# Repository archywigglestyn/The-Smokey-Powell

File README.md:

# The-Smokey-Powell
The Particle Photon Wifi Blynk controlled BBQ Smoker controller

This controller reads temperature through a thermistor. Control of your smokers heat is made through a fan or
Solid State relay. It has three extra probe inputs to be used as meat probes.
Wifi is used to connect to the cloud. 

The blynk app is used as the main interface from your phone or mobile device. It is worth noting that all the information runs through the cloud. This means one could be shopping for supplies, while also monitoring ones bbq back at home.

A 4x20 I2c LCD is used as a local display and four buttons as the interface controls.
The local interface is a little clunky. The main interface was intended to be the blynk app.

This controller can use replacement thermistors for Weber iGrill2 grilling thermometer. Or any other thermistor that will work 
with a 10k ohm reference resistor.

For those that use the circuit board I designed. The Outputs are sinking.

Watch The Youtube video for more information.
https://youtu.be/kV1lrQCiiBc

Included are links below or look above in the files.

Version 1.2 Fixes issues with slow internet by using event based communication with blynk compaired to timed.
Also allows smoke percent to be set while in off mode.
Version 1.3, 6-16-19 Renames a variable to an unused name. so that the code will compile.

1.4, 7-4-19 A fellow creator found a variable I forgot to change.
https://go.particle.io/shared_apps/5d1ea377e9731c0017650d83

The Blynk App (Look Above) Download Blynk. In Blynk there is an option take a picture of the QR code.

The circuit board gerber file	(Look Above)  Send this Zip file in to order a board. Board dimensions are 4.75"x2.5"
I may also decide to sell them	 3-29-18 I uploaded V1.1, It has a few minor fixes.

where I have my circuit boards made http://www.pcbunlimited.com/ They are great quality and cheap!
Look for Panel Share. It moves around on the website but it's the cheapest way if you only want one. $19.95 as of 3/15/19

schematic of circuit board	SCH,PDF, and BRD (Look Above)

thingiverse link to make 3d printed cases and DIN mounts https://www.thingiverse.com/thing:3453571

Smokey Powell shopping list:

Bill of Material (Look Above)
digikey (some items are optional) you can use screw terminals or barrel jacks for power, outputs and inputs. Really you can use anything you like that matches the pitch. You could even solder wires directly.
(I have not tested all of the parts on this list yet.)

meat probes, https://www.amazon.com/Weber-iGrill-Pro-Meat-Probe/dp/B01M8LG8U5/ref=sr_1_4?ie=UTF8&qid=1549819424&sr=8-4&keywords=igrill+2+probes

2n2222a or 2n2222 these are cheap and appear to be everywhere except Digikey. Looks like they are becoming obsolete. You will need three of them.	
https://www.amazon.com/2N2222-Plastic-Encapsulate-Power-Transistors-600mA/dp/B06XPWS52G/ref=sr_1_2?ie=UTF8&qid=1530481975&sr=8-2&keywords=2n2222a

This is the particle photon. The brains of the operation.
https://www.amazon.com/Particle-Reprogrammable-Development-Prototyping-Electronics/dp/B016YNU1A0/ref=sr_1_2?ie=UTF8&qid=1550113530&sr=8-2&keywords=photon

Optional items:

5vdc buzzer 12mm use this if you want a microwave like beep for the alarm. Otherwise attach whatever you want to the relay, noise maker, light, spinning flag motor.
	https://www.amazon.com/gp/product/B00B0Q4KKO/ref=oh_aui_detailpage_o02_s00?ie=UTF8&psc=1

SS Relay	these work good if you are going to do some high power electric smoking
	https://www.amazon.com/gp/product/B0087ZTN08/ref=oh_aui_search_detailpage?ie=UTF8&psc=1

Antenna
Add an Antenna for extra range. Be sure to switch the text to external in the program.
	https://www.amazon.com/gp/product/B01GMBUS8O/ref=oh_aui_detailpage_o01_s00?ie=UTF8&psc=1

bbq guru Fan	
If you want to use a fan. This is an option. although it does not like pwm so you need to set the pulse range threshold to 100. Otherwise many 12vdc pc fans work well at about 30%
https://www.bbqguru.com/storenav?CategoryId=2&ProductId=44

The connectors I used for the screen
https://www.amazon.com/Hilitchi-JST-XHP-housing-Connector-Adapter/dp/B015Y6JOUG/ref=sr_1_3?keywords=2.54+head+connector&qid=1551144713&s=gateway&sr=8-3

Dayton 3FRG5 DC Blower, 12 VDC, 57 CFM. This is a Big blower. The screen dims on my controller when it starts. works well with PWM.
https://www.amazon.com/gp/product/B004KFI6HK/ref=ppx_yo_dt_b_asin_title_o00_s00?ie=UTF8&psc=1

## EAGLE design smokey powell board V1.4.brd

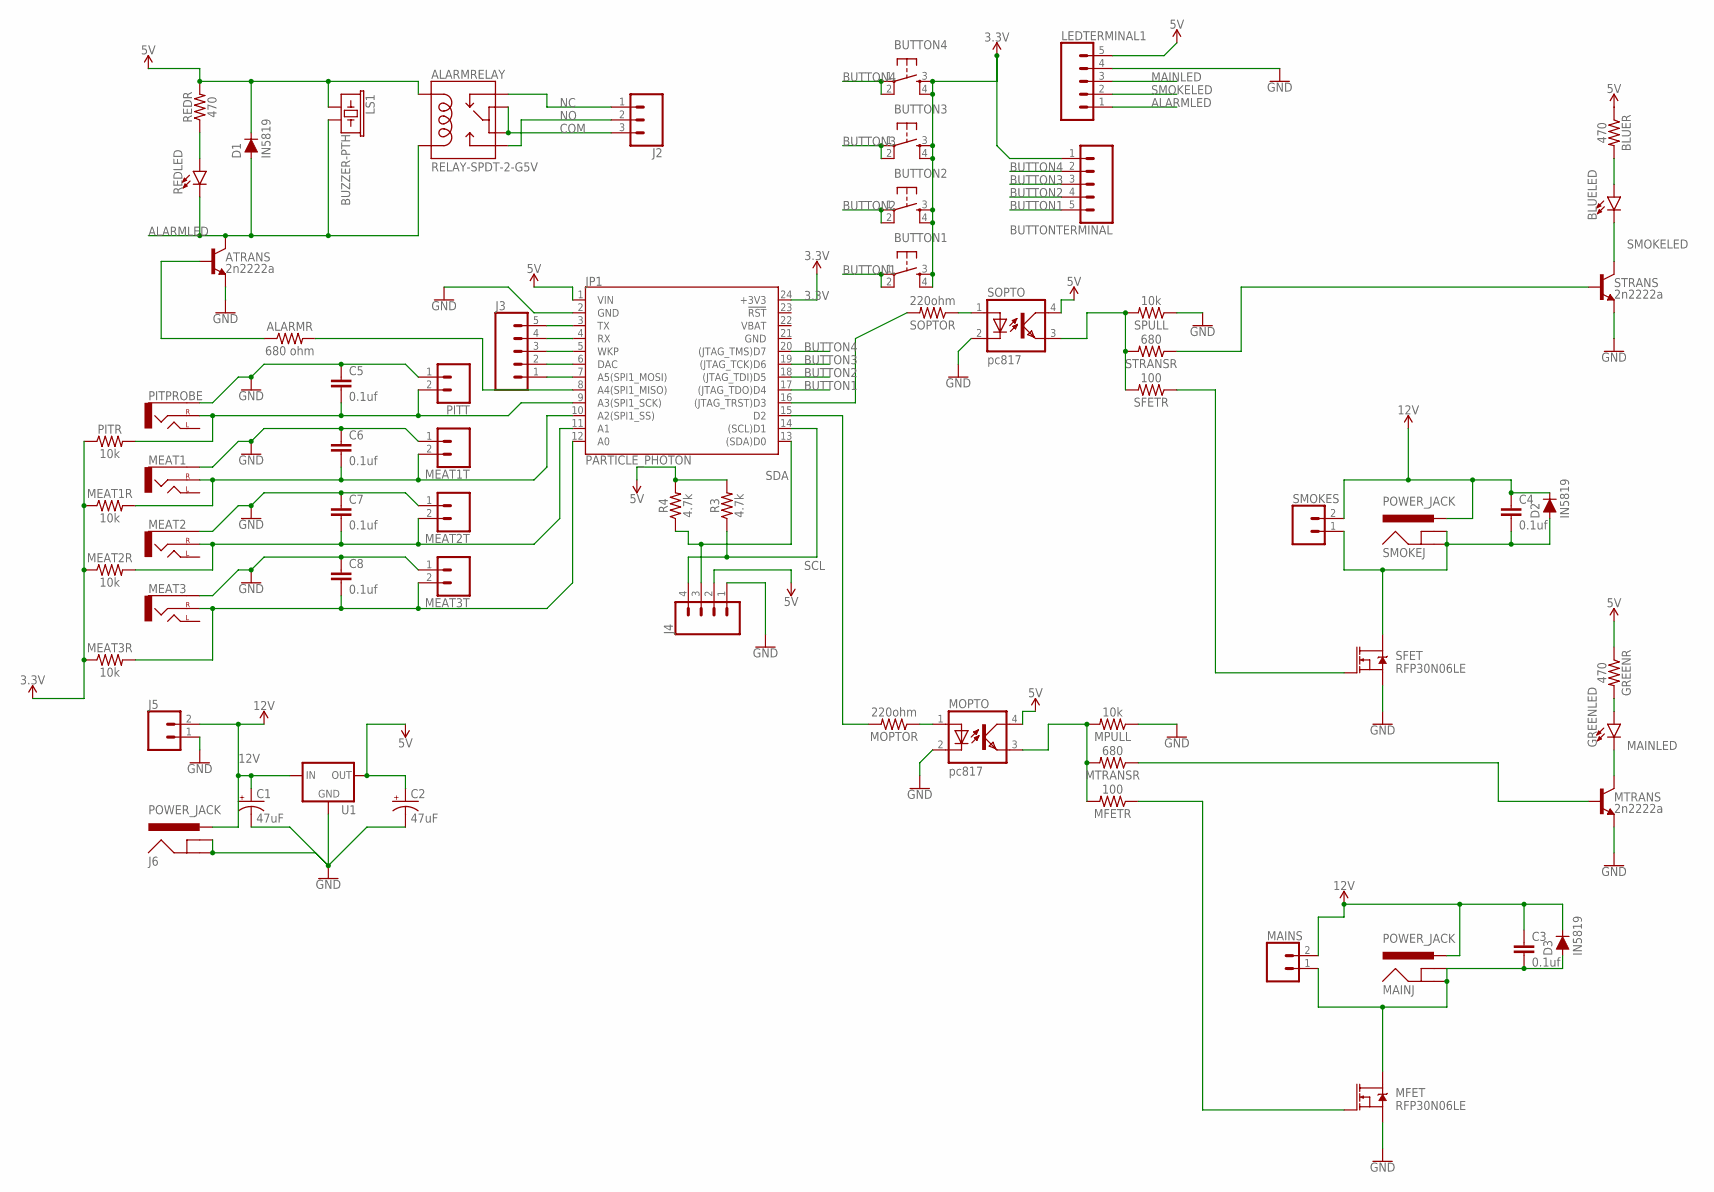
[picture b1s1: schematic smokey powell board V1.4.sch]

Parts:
ALARMR: 680 ohm; AXIAL-0.3
ALARMRELAY: RELAY-SPDT-2-G5V; RELAY-G5V
ATRANS: 2n2222a; TO-92
BLUELED: LED5MM; LED_5MM
BLUER: 470; AXIAL-0.3
BUTTON1, BUTTON2, BUTTON3, BUTTON4: TAC_SWITCHPTH; TACTILE-PTH
BUTTONTERMINAL: CONN_05PTH_LONGPADS; 1X05_LONGPADS
C1, C2: 47uF; CPOL-RADIAL-2.5MM-6.5MM
C3, C4, C5, C6, C7, C8: 0.1uf; C2.5-2
D1, D2, D3: IN5819; DIODE-1N4001
GREENLED: LED5MM; LED_5MM
GREENR: 470; AXIAL-0.3
J2: CONN_03-SCREW-5MM; SCREWTERMINAL-5MM-3
J3: CONN_05; 1X05
J4: CONN_04LONGPADS; 1X04_LONGPADS
J5: CONN_025MM; SCREWTERMINAL-5MM-2
J6: POWER_JACK; POWER_JACK_PTH
JP1: PARTICLE_PHOTON
LEDTERMINAL1: CONN_05PTH_LONGPADS; 1X05_LONGPADS
LS1: BUZZER-PTH; BUZZER-12MM
MAINJ: POWER_JACK; POWER_JACK_PTH
MAINS: CONN_025MM; SCREWTERMINAL-5MM-2
MEAT1, MEAT2, MEAT3: AUDIO_JACK_2.5MM_2.5MM; STEREOJACK2.5MM_STEREOJACK2.5MM
MEAT1R, MEAT2R, MEAT3R: 10k; AXIAL-0.3
MEAT1T, MEAT2T, MEAT3T: CONN_02PTH3; 1X02_LONGPADS
MFET: RFP30N06LE; TO220V
MFETR: 100; AXIAL-0.3
MOPTO: pc817; DIP4
MOPTOR: 220ohm; AXIAL-0.3
MPULL: 10k; AXIAL-0.3
MTRANS: 2n2222a; TO-92
MTRANSR: 680; AXIAL-0.3
PITPROBE: AUDIO_JACK_2.5MM_2.5MM; STEREOJACK2.5MM_STEREOJACK2.5MM
PITR: 10k; AXIAL-0.3
PITT: CONN_02PTH3; 1X02_LONGPADS
R3, R4: 4.7k; AXIAL-0.3
REDLED: LED5MM; LED_5MM
REDR: 470; AXIAL-0.3
SFET: RFP30N06LE; TO220V
SFETR: 100; AXIAL-0.3
SMOKEJ: POWER_JACK; POWER_JACK_PTH
SMOKES: CONN_025MM; SCREWTERMINAL-5MM-2
SOPTO: pc817; DIP4
SOPTOR: 220ohm; AXIAL-0.3
SPULL: 10k; AXIAL-0.3
STRANS: 2n2222a; TO-92
STRANSR: 680; AXIAL-0.3
U1: V_REG_78XXSINK; TO220-IGO

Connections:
3.3V: BUTTON1.3, BUTTON1.4, BUTTON2.3, BUTTON2.4, BUTTON3.3, BUTTON3.4, BUTTON4.3, BUTTON4.4, BUTTONTERMINAL.1, JP1.24 (+3V3), MEAT1R.P$1 (1), MEAT2R.P$1 (1), MEAT3R.P$1 (1), PITR.P$1 (1)
5V: ALARMRELAY.2, BLUER.P$1 (1), C2.1 (+), D1.C, GREENR.P$1 (1), J4.2, JP1.1 (VIN), LEDTERMINAL1.5, LS1.+ (1), MOPTO.4 (COL), R3.P$2 (2), R4.P$2 (2), REDR.P$2 (2), SOPTO.4 (COL), U1.OUT
12V: C1.1 (+), C3.1, C4.1, D2.C, D3.C, J5.2, J6.PWR, MAINJ.PWR, MAINS.2, SMOKEJ.PWR, SMOKES.2, U1.IN
ALARMLED: ALARMRELAY.9, ATRANS.1 (C), D1.A, LEDTERMINAL1.1, LS1.- (2), REDLED.K (C)
BUTTON1: BUTTON1.1, BUTTON1.2, BUTTONTERMINAL.5, JP1.17 ((JTAG_TDO)D4)
BUTTON2: BUTTON2.1, BUTTON2.2, BUTTONTERMINAL.4, JP1.18 ((JTAG_TDI)D5)
BUTTON3: BUTTON3.1, BUTTON3.2, BUTTONTERMINAL.3, JP1.19 ((JTAG_TCK)D6)
BUTTON4: BUTTON4.1, BUTTON4.2, BUTTONTERMINAL.2, JP1.20 ((JTAG_TMS)D7)
COM: ALARMRELAY.5, ALARMRELAY.6, J2.3
GND: ATRANS.3 (E), C1.2 (-), C2.2 (-), C5.1, C6.1, C7.1, C8.1, J4.1, J5.1, J6.GND, J6.GNDBREAK, JP1.2 (GND), JP1.21 (GND), LEDTERMINAL1.4, MEAT1.RING1 (SLEEVE), MEAT1T.1, MEAT2.RING1 (SLEEVE), MEAT2T.1, MEAT3.RING1 (SLEEVE), MEAT3T.1, MFET.3 (S), MOPTO.2 (C), MPULL.P$1 (1), MTRANS.3 (E), PITPROBE.RING1 (SLEEVE), PITT.1, SFET.3 (S), SOPTO.2 (C), SPULL.P$1 (1), STRANS.3 (E), U1.GND
MAINLED: GREENLED.K (C), LEDTERMINAL1.3, MTRANS.1 (C)
unnamed: C7.2, JP1.11 (A1), MEAT2.TIP (RIGHT), MEAT2R.P$2 (2), MEAT2T.2
unnamed: ALARMR.P$2 (2), JP1.8 (A4(SPI1_MISO))
unnamed: MTRANS.2 (B), MTRANSR.P$1 (1)
unnamed: ALARMR.P$1 (1), ATRANS.2 (B)
unnamed: STRANS.2 (B), STRANSR.P$1 (1)
unnamed: J3.5, JP1.3 (TX)
unnamed: J3.4, JP1.4 (RX)
unnamed: J3.3, JP1.5 (WKP)
unnamed: J3.2, JP1.6 (DAC)
unnamed: J3.1, JP1.7 (A5(SPI1_MOSI))
unnamed: MFET.1 (G), MFETR.P$1 (1)
unnamed: C3.2, D3.A, MAINJ.GND, MAINJ.GNDBREAK, MAINS.1, MFET.2 (D)
unnamed: JP1.16 ((JTAG_TRST)D3), SOPTOR.P$2 (2)
unnamed: JP1.15 (D2), MOPTOR.P$2 (2)
unnamed: SOPTO.1 (A), SOPTOR.P$1 (1)
unnamed: MOPTO.1 (A), MOPTOR.P$1 (1)
unnamed: MFETR.P$2 (2), MOPTO.3 (EMIT), MPULL.P$2 (2), MTRANSR.P$2 (2)
unnamed: SFETR.P$2 (2), SOPTO.3 (EMIT), SPULL.P$2 (2), STRANSR.P$2 (2)
unnamed: SFET.1 (G), SFETR.P$1 (1)
unnamed: REDLED.A, REDR.P$1 (1)
unnamed: C4.2, D2.A, SFET.2 (D), SMOKEJ.GND, SMOKEJ.GNDBREAK, SMOKES.1
unnamed: BLUELED.A, BLUER.P$2 (2)
unnamed: GREENLED.A, GREENR.P$2 (2)
unnamed: C8.2, JP1.12 (A0), MEAT3.TIP (RIGHT), MEAT3R.P$2 (2), MEAT3T.2
unnamed: C6.2, JP1.10 (A2(SPI1_SS)), MEAT1.TIP (RIGHT), MEAT1R.P$2 (2), MEAT1T.2
unnamed: C5.2, JP1.9 (A3(SPI1_SCK)), PITPROBE.TIP (RIGHT), PITR.P$2 (2), PITT.2
NC: ALARMRELAY.1, J2.1
NO: ALARMRELAY.10, J2.2
SCL: J4.4, JP1.14 ((SCL)D1), R3.P$1 (1)
SDA: J4.3, JP1.13 ((SDA)D0), R4.P$1 (1)
SMOKELED: BLUELED.K (C), LEDTERMINAL1.2, STRANS.1 (C)
VBAT: JP1.22 (VBAT)

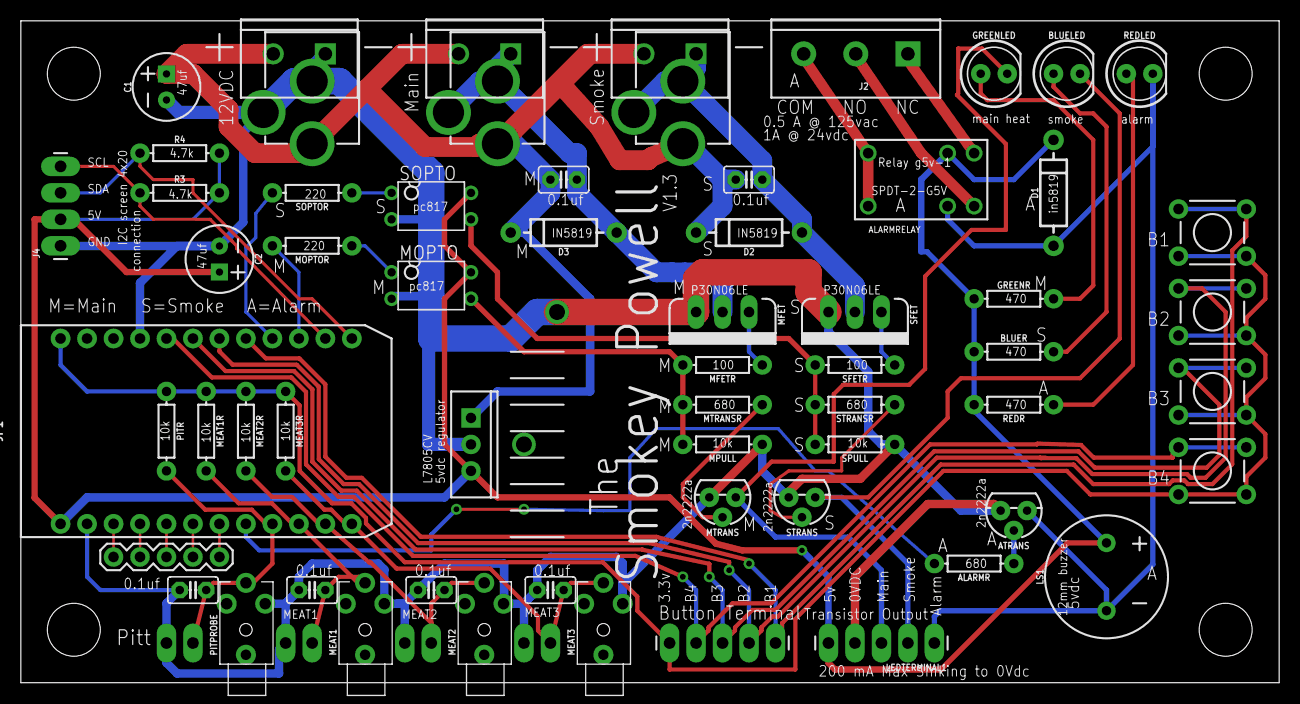
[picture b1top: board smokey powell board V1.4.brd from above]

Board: 2 copper layers, 120.7 x 63.5 mm, 66 parts (0 on the bottom side), 42 nets.

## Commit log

2018-07-08 Add files via upload
    This is the parts list for the circuit board
2018-07-08 gerber files for making a circuit board
    Send this Zip in and order a board Board dimensions are 4.5"x2.5"
2018-07-08 Circuit board schematic
2018-07-08 Bill Of Meterial
    Not everything on this list is needed. The board can accept barrel jacks and screw terminals for example.
2018-07-08 Blynk program
    Scan this with the Blynk app to open the Smokey Powell interface. you will need to purchase some points to run it.
2018-07-23 Circuit board gerber file
    Send this file in to have a circuit board made. It cost me under $20 to make one
2018-07-23 Blynk App program
    add this to your Blynk app to get the interface working. Use the Blynk app to take a picture of it. Don't forget to add your Blynk auth code to your sketch.
2019-02-11 Rename Smokey Powell BOM.csv to Bill of material
2019-03-30 Add files via upload
    Send this file in to have a board fabricated.
2019-03-30 Add files via upload
    Gerber Files for ordering a circuit board. V1.3 Added a 5v pin to the transistor area for powering the unit externally from a 5vdc power supply.

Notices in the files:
parts and their libraries:
SparkFun-Retired: Licensing: Creative Commons ShareAlike 4.0 International - https://creativecommons.org/licenses/by-sa/4.0
